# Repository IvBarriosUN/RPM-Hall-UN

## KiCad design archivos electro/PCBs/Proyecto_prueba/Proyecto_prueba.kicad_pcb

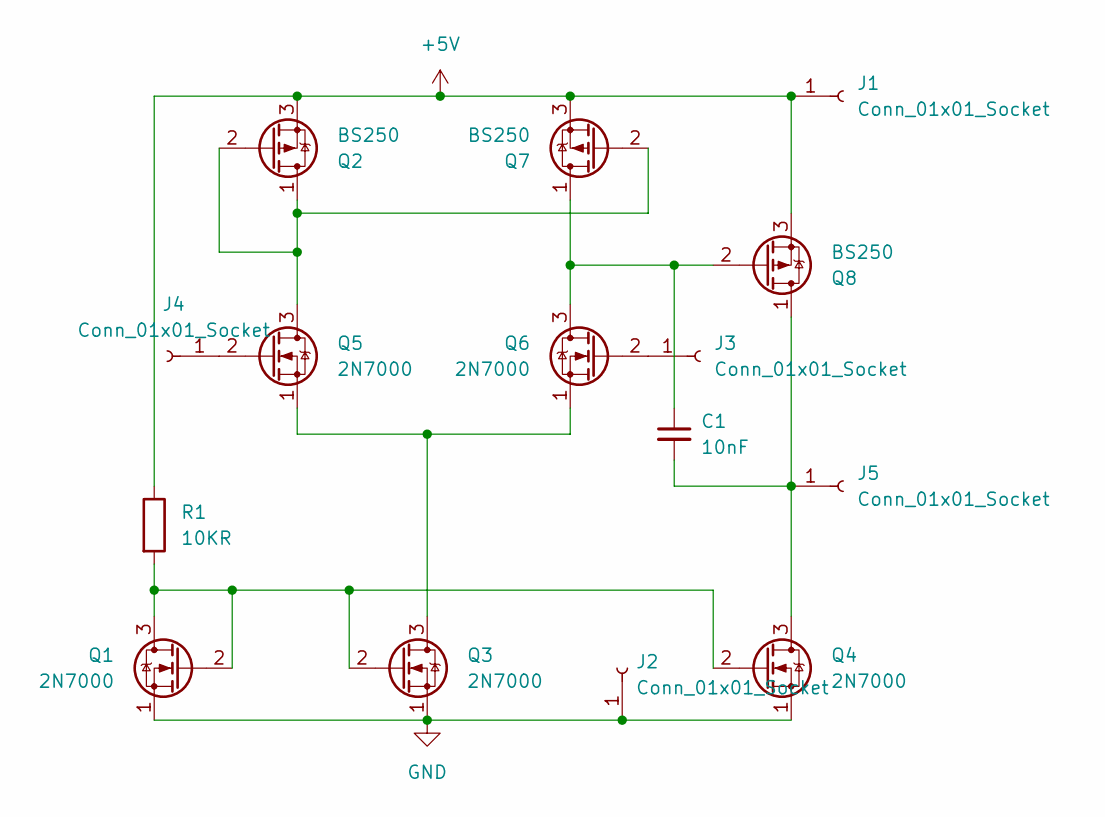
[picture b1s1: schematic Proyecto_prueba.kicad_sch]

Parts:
C1: 10nF; C_Disc_D3.0mm_W1.6mm_P2.50mm
J1, J2, J3, J4, J5: Conn_01x01_Socket; PinHeader_1x01_P2.54mm_Vertical
Q1, Q3, Q4, Q5, Q6: 2N7000; TO-92_Inline
Q2, Q7, Q8: BS250; TO-92_Inline
R1: 10KR; R_Axial_DIN0204_L3.6mm_D1.6mm_P5.08mm_Horizontal

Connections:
+5V: J1.1, Q2.3 (S), Q7.3 (S), Q8.3 (S), R1.1
GND: J2.1, Q1.1 (S), Q3.1 (S), Q4.1 (S)
unnamed: J3.1, Q6.2 (G)
unnamed: J4.1, Q5.2 (G)
unnamed: C1.2, J5.1, Q4.3 (D), Q8.1 (D)
unnamed: Q1.2 (G), Q1.3 (D), Q3.2 (G), Q4.2 (G), R1.2
unnamed: Q2.1 (D), Q2.2 (G), Q5.3 (D), Q7.2 (G)
unnamed: Q3.3 (D), Q5.1 (S), Q6.1 (S)
unnamed: C1.1, Q6.3 (D), Q7.1 (D), Q8.2 (G)

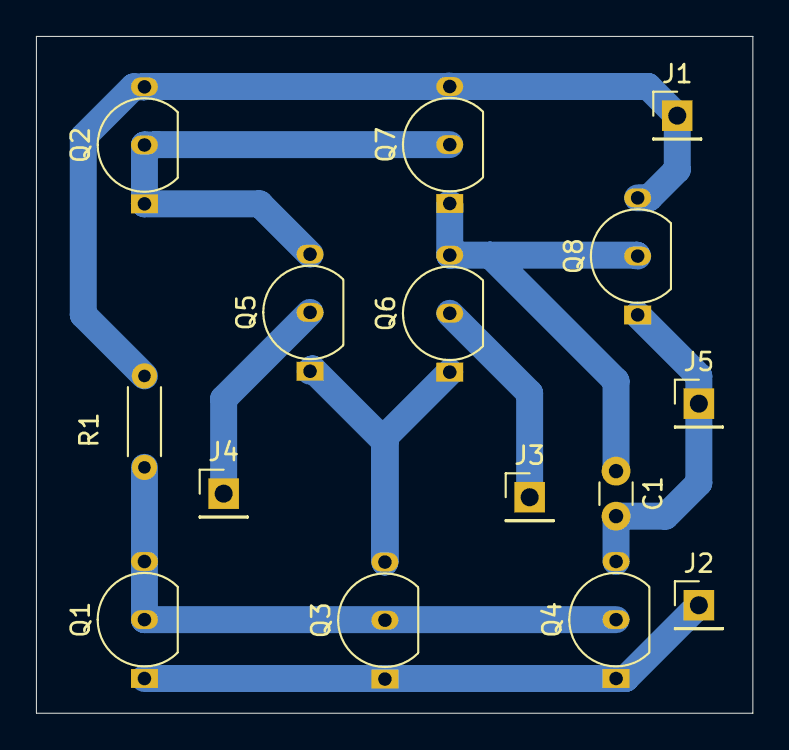
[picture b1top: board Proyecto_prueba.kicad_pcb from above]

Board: 2 copper layers, 39.8 x 37.6 mm, 15 parts (0 on the bottom side), 9 nets.

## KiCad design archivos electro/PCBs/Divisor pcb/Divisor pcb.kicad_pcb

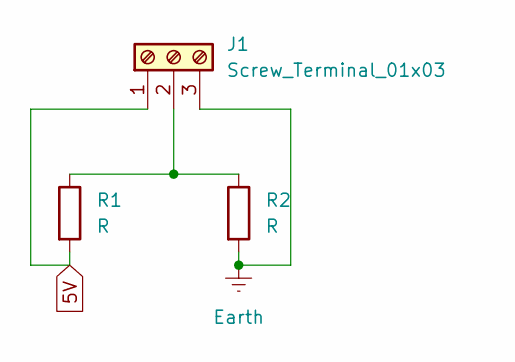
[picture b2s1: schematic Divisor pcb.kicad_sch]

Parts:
J1: Screw_Terminal_01x03; TerminalBlock_bornier-3_P5.08mm
R1, R2: R; R_Axial_DIN0309_L9.0mm_D3.2mm_P12.70mm_Horizontal

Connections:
5V: J1.1, R1.2
Earth: J1.3, R2.2
unnamed: J1.2, R1.1, R2.1

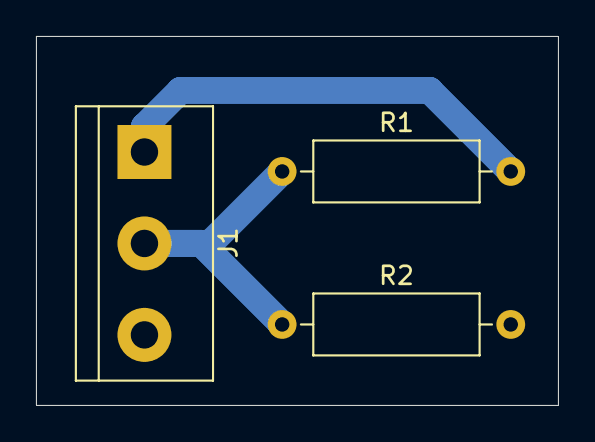
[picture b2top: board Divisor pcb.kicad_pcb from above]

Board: 2 copper layers, 29.0 x 20.5 mm, 3 parts (0 on the bottom side), 3 nets.

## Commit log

2025-06-05 Create Cuaderno
